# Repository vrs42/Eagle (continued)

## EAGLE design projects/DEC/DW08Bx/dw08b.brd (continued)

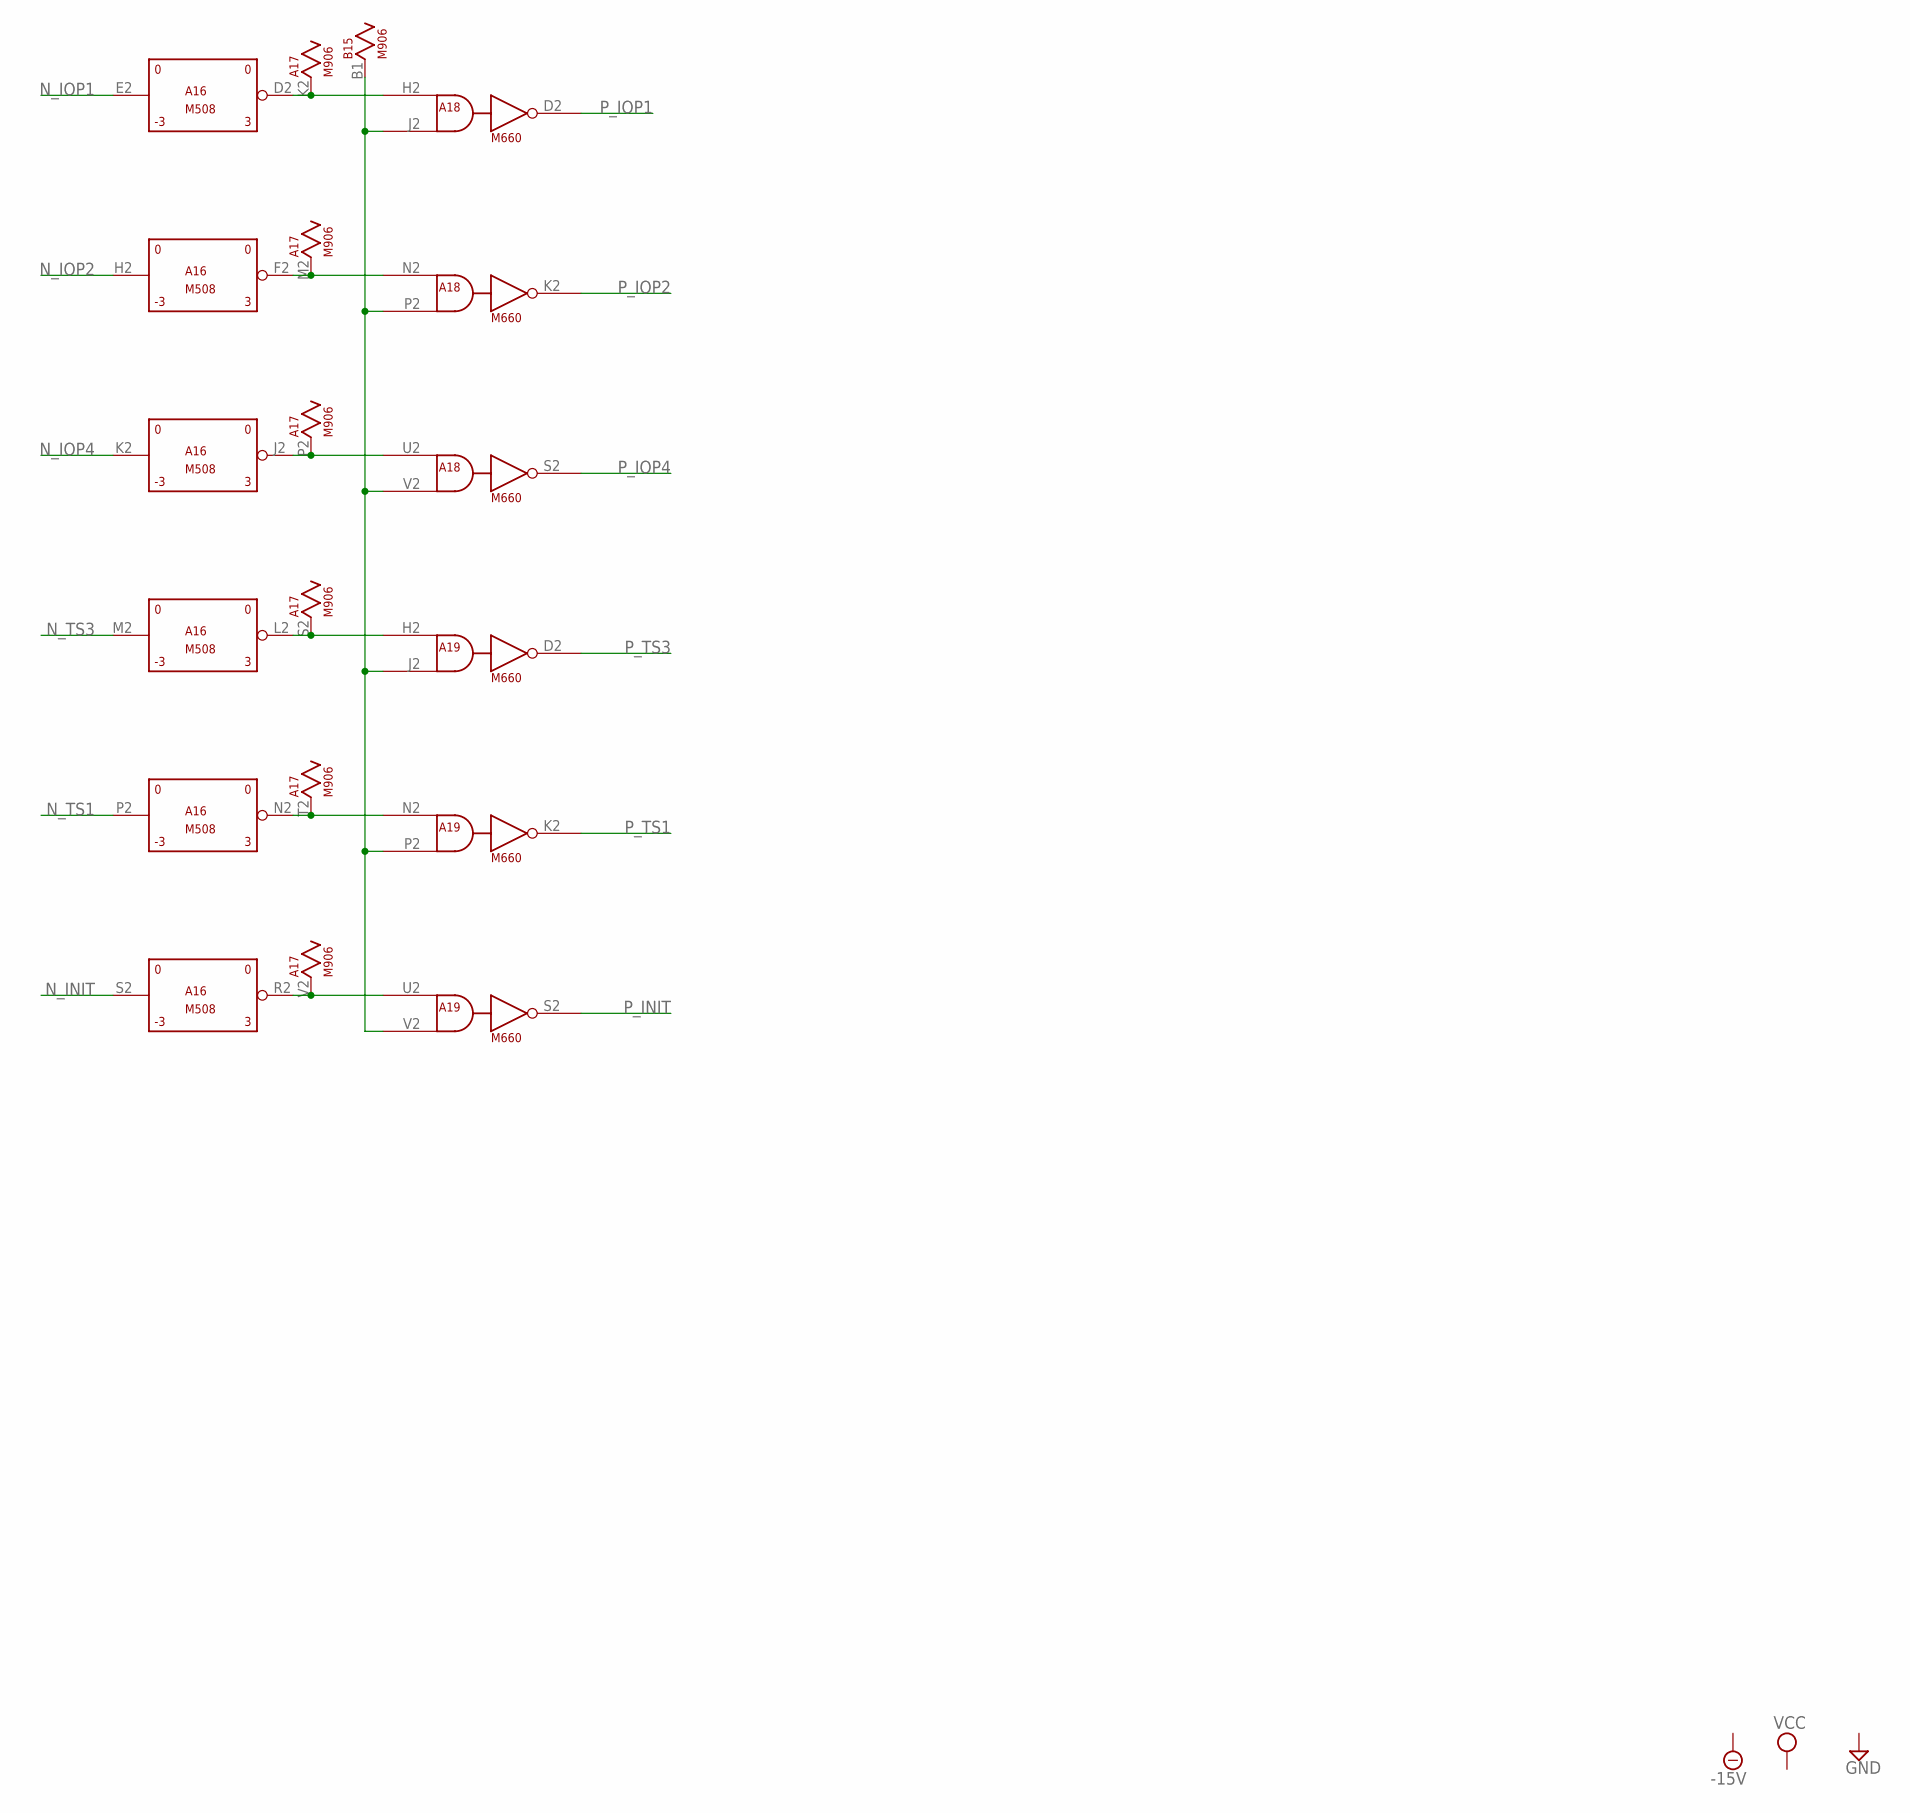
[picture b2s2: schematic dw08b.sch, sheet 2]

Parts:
A16: M508; H807
A17: M906; H807
A18, A19: M660; H807
B15: M906; H807

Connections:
-15V: A16.B2 (-15V); also elsewhere on the board
GND: A16.C2 (GND), A17.A1 (GND), A17.C1 (GND), A17.C2 (GND), A17.F1 (GND), A17.F2 (GND), A17.J2 (GND), A17.K1 (GND), A17.L2 (GND), A17.N1 (GND), A17.N2 (GND), A17.R1 (GND), A17.R2 (GND), A17.T1 (GND), A17.U2 (GND), A18.C2 (GND), A19.C2 (GND), B15.A1 (GND), B15.C1 (GND), B15.C2 (GND), B15.F1 (GND), B15.F2 (GND), B15.J2 (GND), B15.K1 (GND), B15.L2 (GND), B15.N1 (GND), B15.N2 (GND), B15.R1 (GND), B15.R2 (GND), B15.T1 (GND), B15.U2 (GND); also elsewhere on the board
unnamed: A16.D2 (OUT), A17.K2, A18.H2 (IN1)
unnamed: A16.F2 (OUT), A17.M2, A18.N2 (IN1)
unnamed: A16.J2 (OUT), A17.P2, A18.U2 (IN1)
unnamed: A16.L2 (OUT), A17.S2, A19.H2 (IN1)
unnamed: A16.N2 (OUT), A17.T2, A19.N2 (IN1)
unnamed: A16.R2 (OUT), A17.V2, A19.U2 (IN1)
unnamed: A18.J2 (IN2), A18.P2 (IN2), A18.V2 (IN2), A19.J2 (IN2), A19.P2 (IN2), A19.V2 (IN2), B15.B1
N_INIT: A16.S2 (IN); also elsewhere on the board
N_IOP1: A16.E2 (IN); also elsewhere on the board
N_IOP2: A16.H2 (IN); also elsewhere on the board
N_IOP4: A16.K2 (IN); also elsewhere on the board
N_TS1: A16.P2 (IN); also elsewhere on the board
N_TS3: A16.M2 (IN); also elsewhere on the board
P_INIT: A19.S2 (OUT); also elsewhere on the board
P_IOP1: A18.D2 (OUT); also elsewhere on the board
P_IOP2: A18.K2 (OUT); also elsewhere on the board
P_IOP4: A18.S2 (OUT); also elsewhere on the board
P_TS1: A19.K2 (OUT); also elsewhere on the board
P_TS3: A19.D2 (OUT); also elsewhere on the board
VCC: A16.A2 (VCC), A17.A2 (VCC), A18.A2 (VCC), A19.A2 (VCC), B15.A2 (VCC); also elsewhere on the board

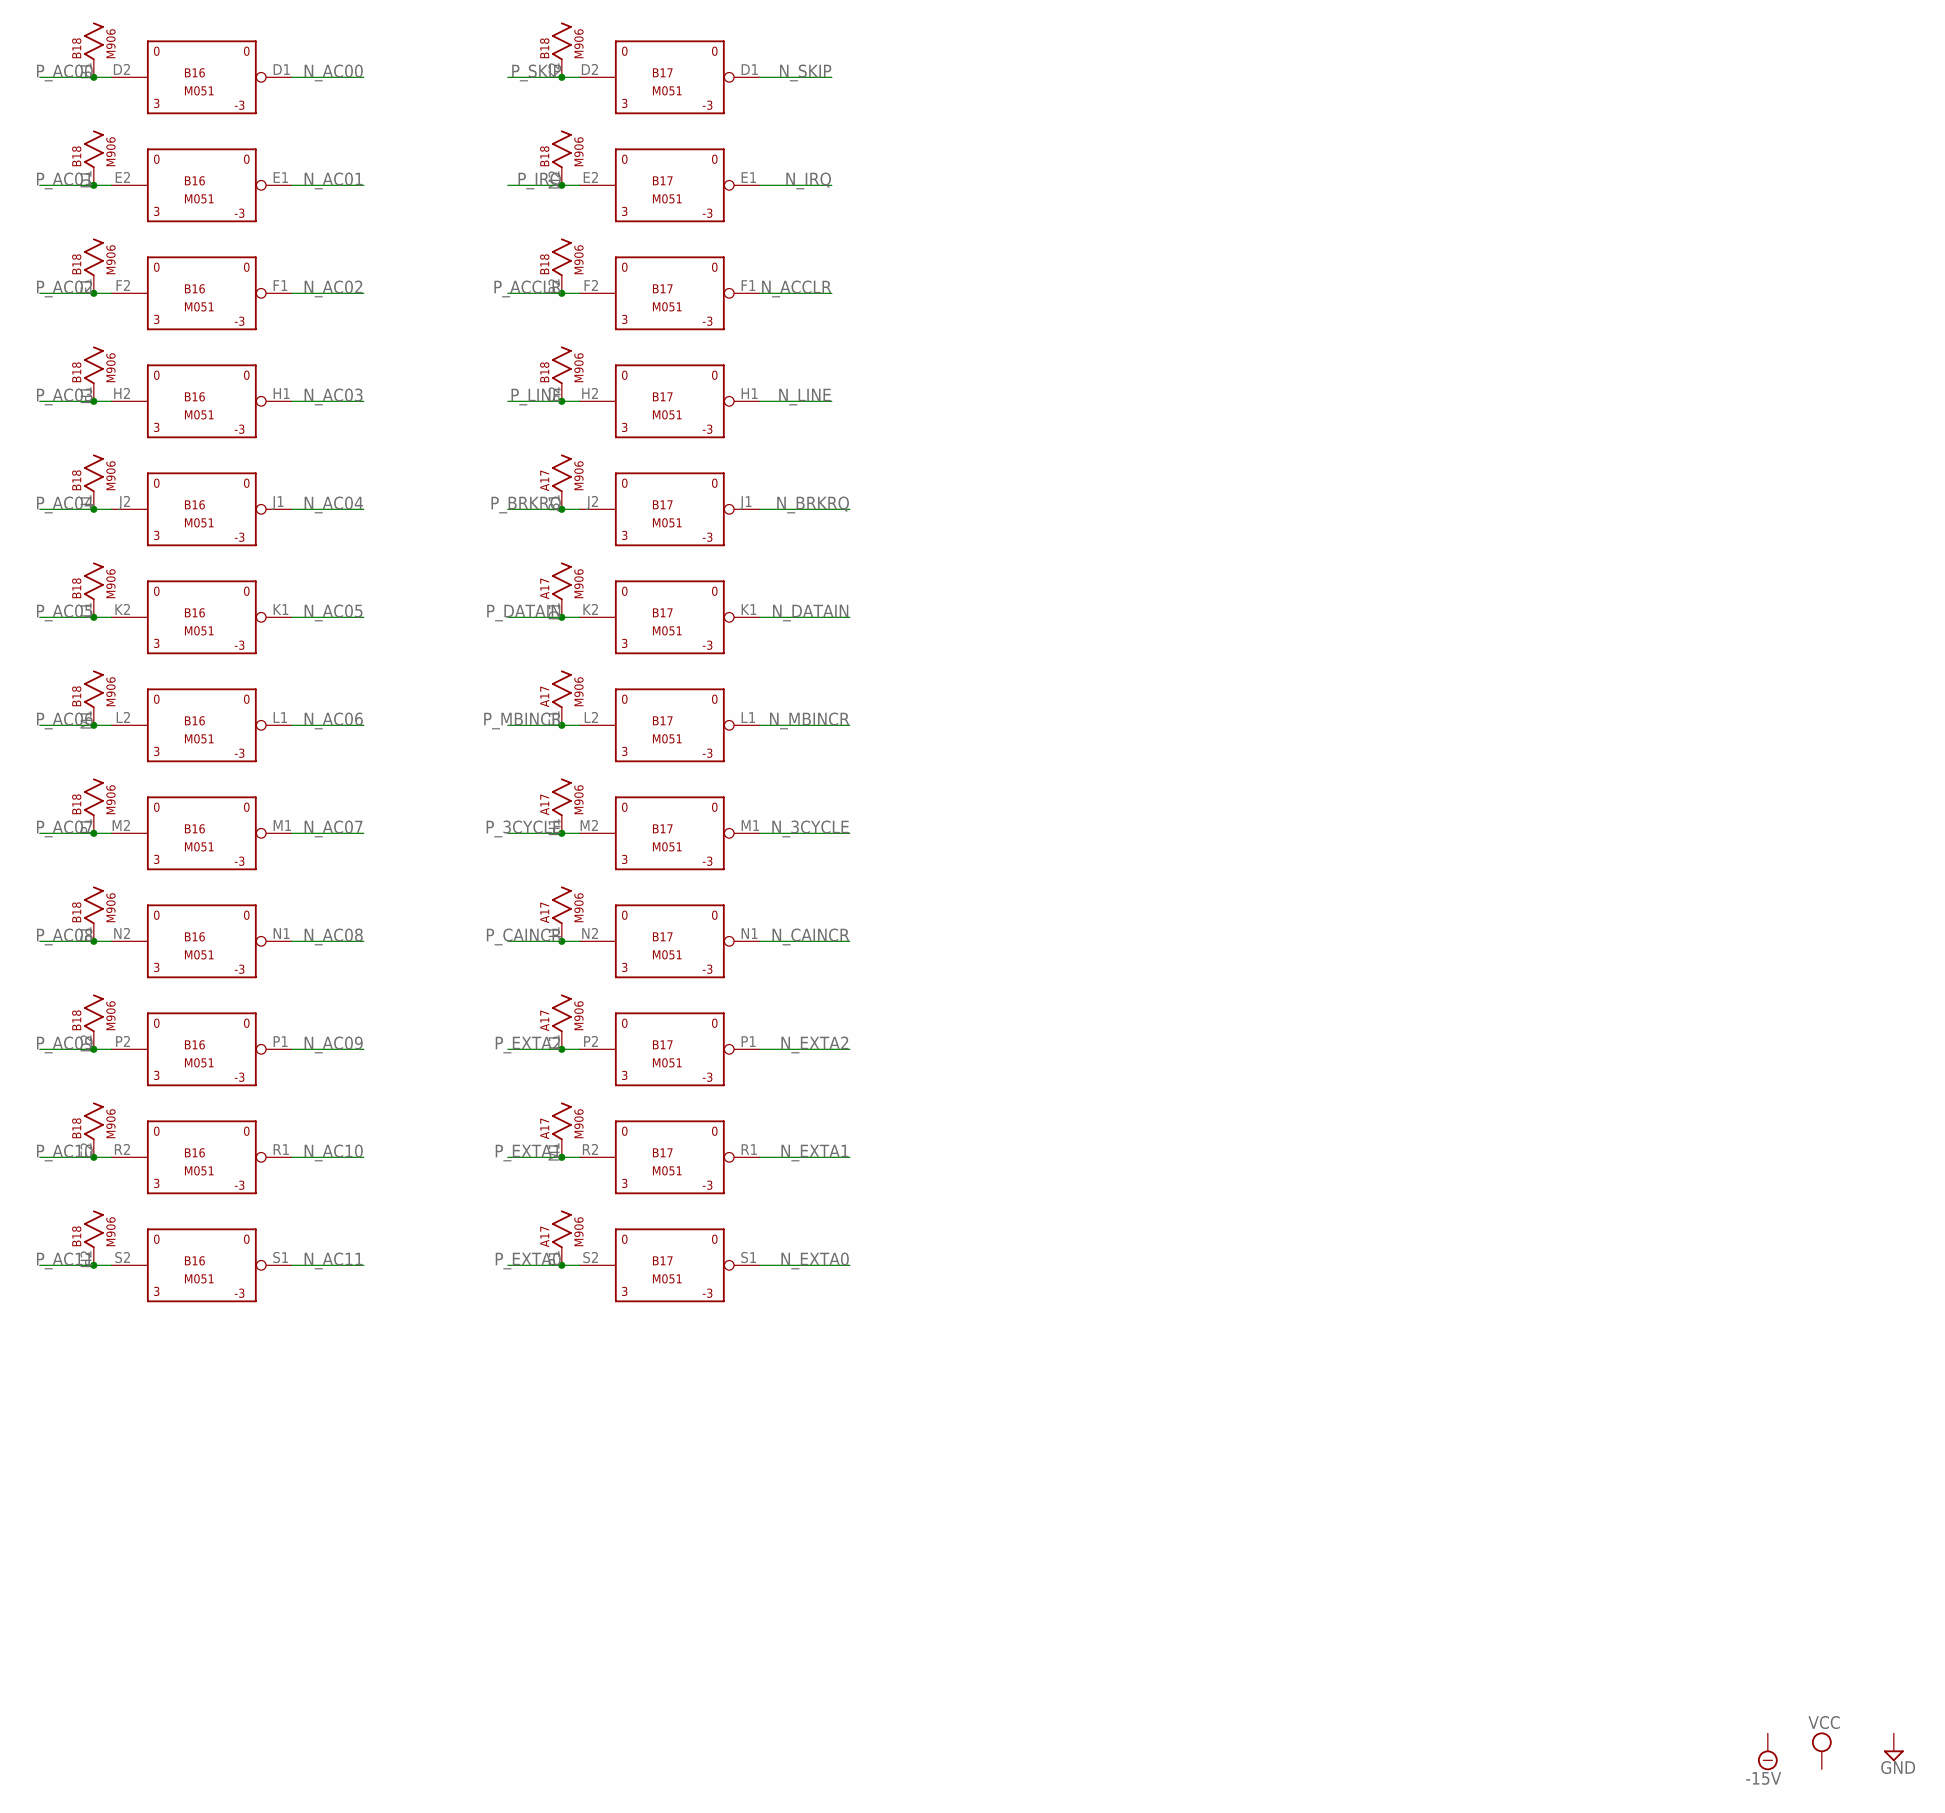
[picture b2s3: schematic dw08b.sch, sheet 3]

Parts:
A17: M906; H807
B16, B17: M051; H807
B18: M906; H807

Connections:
-15V: B16.B2 (-15V), B17.B2 (-15V); also elsewhere on the board
GND: A17.A1 (GND), A17.C1 (GND), A17.C2 (GND), A17.F1 (GND), A17.F2 (GND), A17.J2 (GND), A17.K1 (GND), A17.L2 (GND), A17.N1 (GND), A17.N2 (GND), A17.R1 (GND), A17.R2 (GND), A17.T1 (GND), A17.U2 (GND), B16.C2 (GND), B16.T1 (GND), B17.C2 (GND), B17.T1 (GND), B18.A1 (GND), B18.C1 (GND), B18.C2 (GND), B18.F1 (GND), B18.F2 (GND), B18.J2 (GND), B18.K1 (GND), B18.L2 (GND), B18.N1 (GND), B18.N2 (GND), B18.R1 (GND), B18.R2 (GND), B18.T1 (GND), B18.U2 (GND); also elsewhere on the board
N_3CYCLE: B17.M1 (OUT); also elsewhere on the board
N_AC00: B16.D1 (OUT); also elsewhere on the board
N_AC01: B16.E1 (OUT); also elsewhere on the board
N_AC02: B16.F1 (OUT); also elsewhere on the board
N_AC03: B16.H1 (OUT); also elsewhere on the board
N_AC04: B16.J1 (OUT); also elsewhere on the board
N_AC05: B16.K1 (OUT); also elsewhere on the board
N_AC06: B16.L1 (OUT); also elsewhere on the board
N_AC07: B16.M1 (OUT); also elsewhere on the board
N_AC08: B16.N1 (OUT); also elsewhere on the board
N_AC09: B16.P1 (OUT); also elsewhere on the board
N_AC10: B16.R1 (OUT); also elsewhere on the board
N_AC11: B16.S1 (OUT); also elsewhere on the board
N_ACCLR: B17.F1 (OUT); also elsewhere on the board
N_BRKRQ: B17.J1 (OUT); also elsewhere on the board
N_CAINCR: B17.N1 (OUT); also elsewhere on the board
N_DATAIN: B17.K1 (OUT); also elsewhere on the board
N_EXTA0: B17.S1 (OUT); also elsewhere on the board
N_EXTA1: B17.R1 (OUT); also elsewhere on the board
N_EXTA2: B17.P1 (OUT); also elsewhere on the board
N_IRQ: B17.E1 (OUT); also elsewhere on the board
N_LINE: B17.H1 (OUT); also elsewhere on the board
N_MBINCR: B17.L1 (OUT); also elsewhere on the board
N_SKIP: B17.D1 (OUT); also elsewhere on the board
P_3CYCLE: A17.H1, B17.M2 (IN); also elsewhere on the board
P_AC00: B16.D2 (IN), B18.B1; also elsewhere on the board
P_AC01: B16.E2 (IN), B18.D1; also elsewhere on the board
P_AC02: B16.F2 (IN), B18.E1; also elsewhere on the board
P_AC03: B16.H2 (IN), B18.H1; also elsewhere on the board
P_AC04: B16.J2 (IN), B18.J1; also elsewhere on the board
P_AC05: B16.K2 (IN), B18.L1; also elsewhere on the board
P_AC06: B16.L2 (IN), B18.M1; also elsewhere on the board
P_AC07: B16.M2 (IN), B18.P1; also elsewhere on the board
P_AC08: B16.N2 (IN), B18.S1; also elsewhere on the board
P_AC09: B16.P2 (IN), B18.D2; also elsewhere on the board
P_AC10: B16.R2 (IN), B18.E2; also elsewhere on the board
P_AC11: B16.S2 (IN), B18.H2; also elsewhere on the board
P_ACCLR: B17.F2 (IN), B18.P2; also elsewhere on the board
P_BRKRQ: A17.B1, B17.J2 (IN); also elsewhere on the board
P_CAINCR: A17.J1, B17.N2 (IN); also elsewhere on the board
P_DATAIN: A17.D1, B17.K2 (IN); also elsewhere on the board
P_EXTA0: A17.P1, B17.S2 (IN); also elsewhere on the board
P_EXTA1: A17.M1, B17.R2 (IN); also elsewhere on the board
P_EXTA2: A17.L1, B17.P2 (IN); also elsewhere on the board
P_IRQ: B17.E2 (IN), B18.M2; also elsewhere on the board
P_LINE: B17.H2 (IN), B18.S2; also elsewhere on the board
P_MBINCR: A17.E1, B17.L2 (IN); also elsewhere on the board
P_SKIP: B17.D2 (IN), B18.K2; also elsewhere on the board
VCC: A17.A2 (VCC), B16.A2 (VCC), B17.A2 (VCC), B18.A2 (VCC); also elsewhere on the board

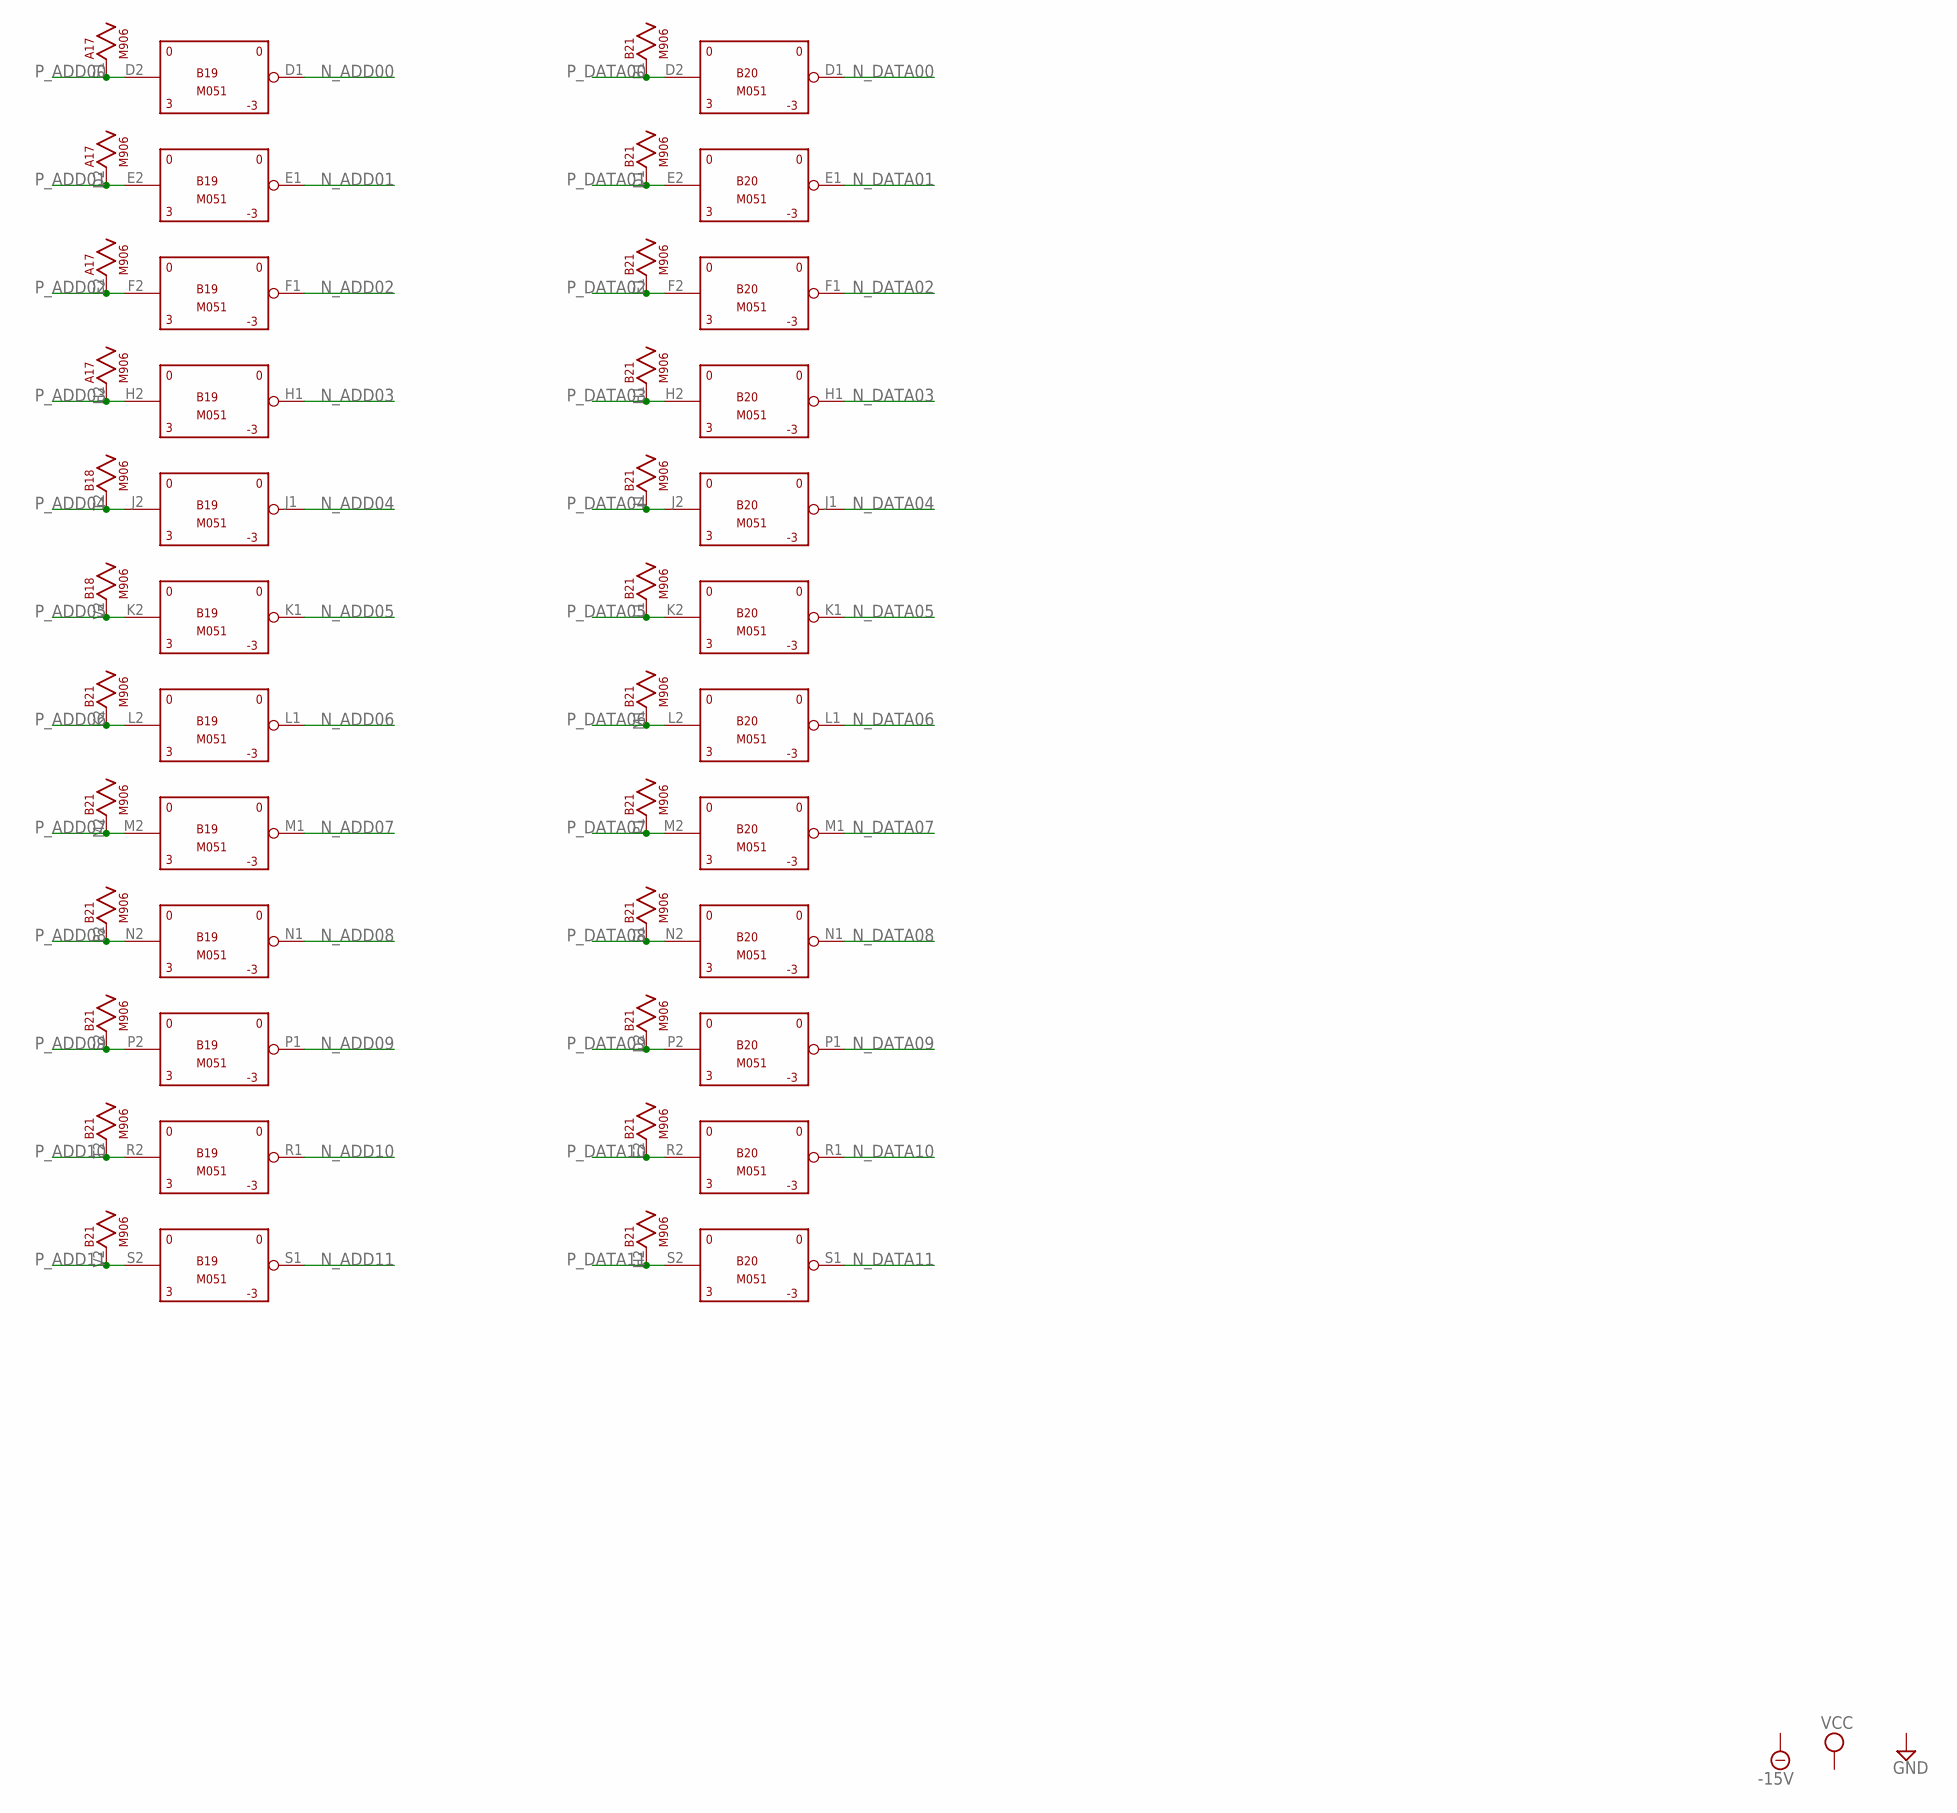
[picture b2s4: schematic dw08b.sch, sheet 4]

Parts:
A17: M906; H807
B18, B21: M906; H807
B19, B20: M051; H807

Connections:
-15V: B19.B2 (-15V), B20.B2 (-15V); also elsewhere on the board
GND: A17.A1 (GND), A17.C1 (GND), A17.C2 (GND), A17.F1 (GND), A17.F2 (GND), A17.J2 (GND), A17.K1 (GND), A17.L2 (GND), A17.N1 (GND), A17.N2 (GND), A17.R1 (GND), A17.R2 (GND), A17.T1 (GND), A17.U2 (GND), B18.A1 (GND), B18.C1 (GND), B18.C2 (GND), B18.F1 (GND), B18.F2 (GND), B18.J2 (GND), B18.K1 (GND), B18.L2 (GND), B18.N1 (GND), B18.N2 (GND), B18.R1 (GND), B18.R2 (GND), B18.T1 (GND), B18.U2 (GND), B19.C2 (GND), B19.T1 (GND), B20.C2 (GND), B20.T1 (GND), B21.A1 (GND), B21.C1 (GND), B21.C2 (GND), B21.F1 (GND), B21.F2 (GND), B21.J2 (GND), B21.K1 (GND), B21.L2 (GND), B21.N1 (GND), B21.N2 (GND), B21.R1 (GND), B21.R2 (GND), B21.T1 (GND), B21.U2 (GND); also elsewhere on the board
N_ADD00: B19.D1 (OUT); also elsewhere on the board
N_ADD01: B19.E1 (OUT); also elsewhere on the board
N_ADD02: B19.F1 (OUT); also elsewhere on the board
N_ADD03: B19.H1 (OUT); also elsewhere on the board
N_ADD04: B19.J1 (OUT); also elsewhere on the board
N_ADD05: B19.K1 (OUT); also elsewhere on the board
N_ADD06: B19.L1 (OUT); also elsewhere on the board
N_ADD07: B19.M1 (OUT); also elsewhere on the board
N_ADD08: B19.N1 (OUT); also elsewhere on the board
N_ADD09: B19.P1 (OUT); also elsewhere on the board
N_ADD10: B19.R1 (OUT); also elsewhere on the board
N_ADD11: B19.S1 (OUT); also elsewhere on the board
N_DATA00: B20.D1 (OUT); also elsewhere on the board
N_DATA01: B20.E1 (OUT); also elsewhere on the board
N_DATA02: B20.F1 (OUT); also elsewhere on the board
N_DATA03: B20.H1 (OUT); also elsewhere on the board
N_DATA04: B20.J1 (OUT); also elsewhere on the board
N_DATA05: B20.K1 (OUT); also elsewhere on the board
N_DATA06: B20.L1 (OUT); also elsewhere on the board
N_DATA07: B20.M1 (OUT); also elsewhere on the board
N_DATA08: B20.N1 (OUT); also elsewhere on the board
N_DATA09: B20.P1 (OUT); also elsewhere on the board
N_DATA10: B20.R1 (OUT); also elsewhere on the board
N_DATA11: B20.S1 (OUT); also elsewhere on the board
P_ADD00: A17.S1, B19.D2 (IN); also elsewhere on the board
P_ADD01: A17.D2, B19.E2 (IN); also elsewhere on the board
P_ADD02: A17.E2, B19.F2 (IN); also elsewhere on the board
P_ADD03: A17.H2, B19.H2 (IN); also elsewhere on the board
P_ADD04: B18.T2, B19.J2 (IN); also elsewhere on the board
P_ADD05: B18.V2, B19.K2 (IN); also elsewhere on the board
P_ADD06: B19.L2 (IN), B21.K2; also elsewhere on the board
P_ADD07: B19.M2 (IN), B21.M2; also elsewhere on the board
P_ADD08: B19.N2 (IN), B21.P2; also elsewhere on the board
P_ADD09: B19.P2 (IN), B21.S2; also elsewhere on the board
P_ADD10: B19.R2 (IN), B21.T2; also elsewhere on the board
P_ADD11: B19.S2 (IN), B21.V2; also elsewhere on the board
P_DATA00: B20.D2 (IN), B21.B1; also elsewhere on the board
P_DATA01: B20.E2 (IN), B21.D1; also elsewhere on the board
P_DATA02: B20.F2 (IN), B21.E1; also elsewhere on the board
P_DATA03: B20.H2 (IN), B21.H1; also elsewhere on the board
P_DATA04: B20.J2 (IN), B21.J1; also elsewhere on the board
P_DATA05: B20.K2 (IN), B21.L1; also elsewhere on the board
P_DATA06: B20.L2 (IN), B21.M1; also elsewhere on the board
P_DATA07: B20.M2 (IN), B21.P1; also elsewhere on the board
P_DATA08: B20.N2 (IN), B21.S1; also elsewhere on the board
P_DATA09: B20.P2 (IN), B21.D2; also elsewhere on the board
P_DATA10: B20.R2 (IN), B21.E2; also elsewhere on the board
P_DATA11: B20.S2 (IN), B21.H2; also elsewhere on the board
VCC: A17.A2 (VCC), B18.A2 (VCC), B19.A2 (VCC), B20.A2 (VCC), B21.A2 (VCC); also elsewhere on the board

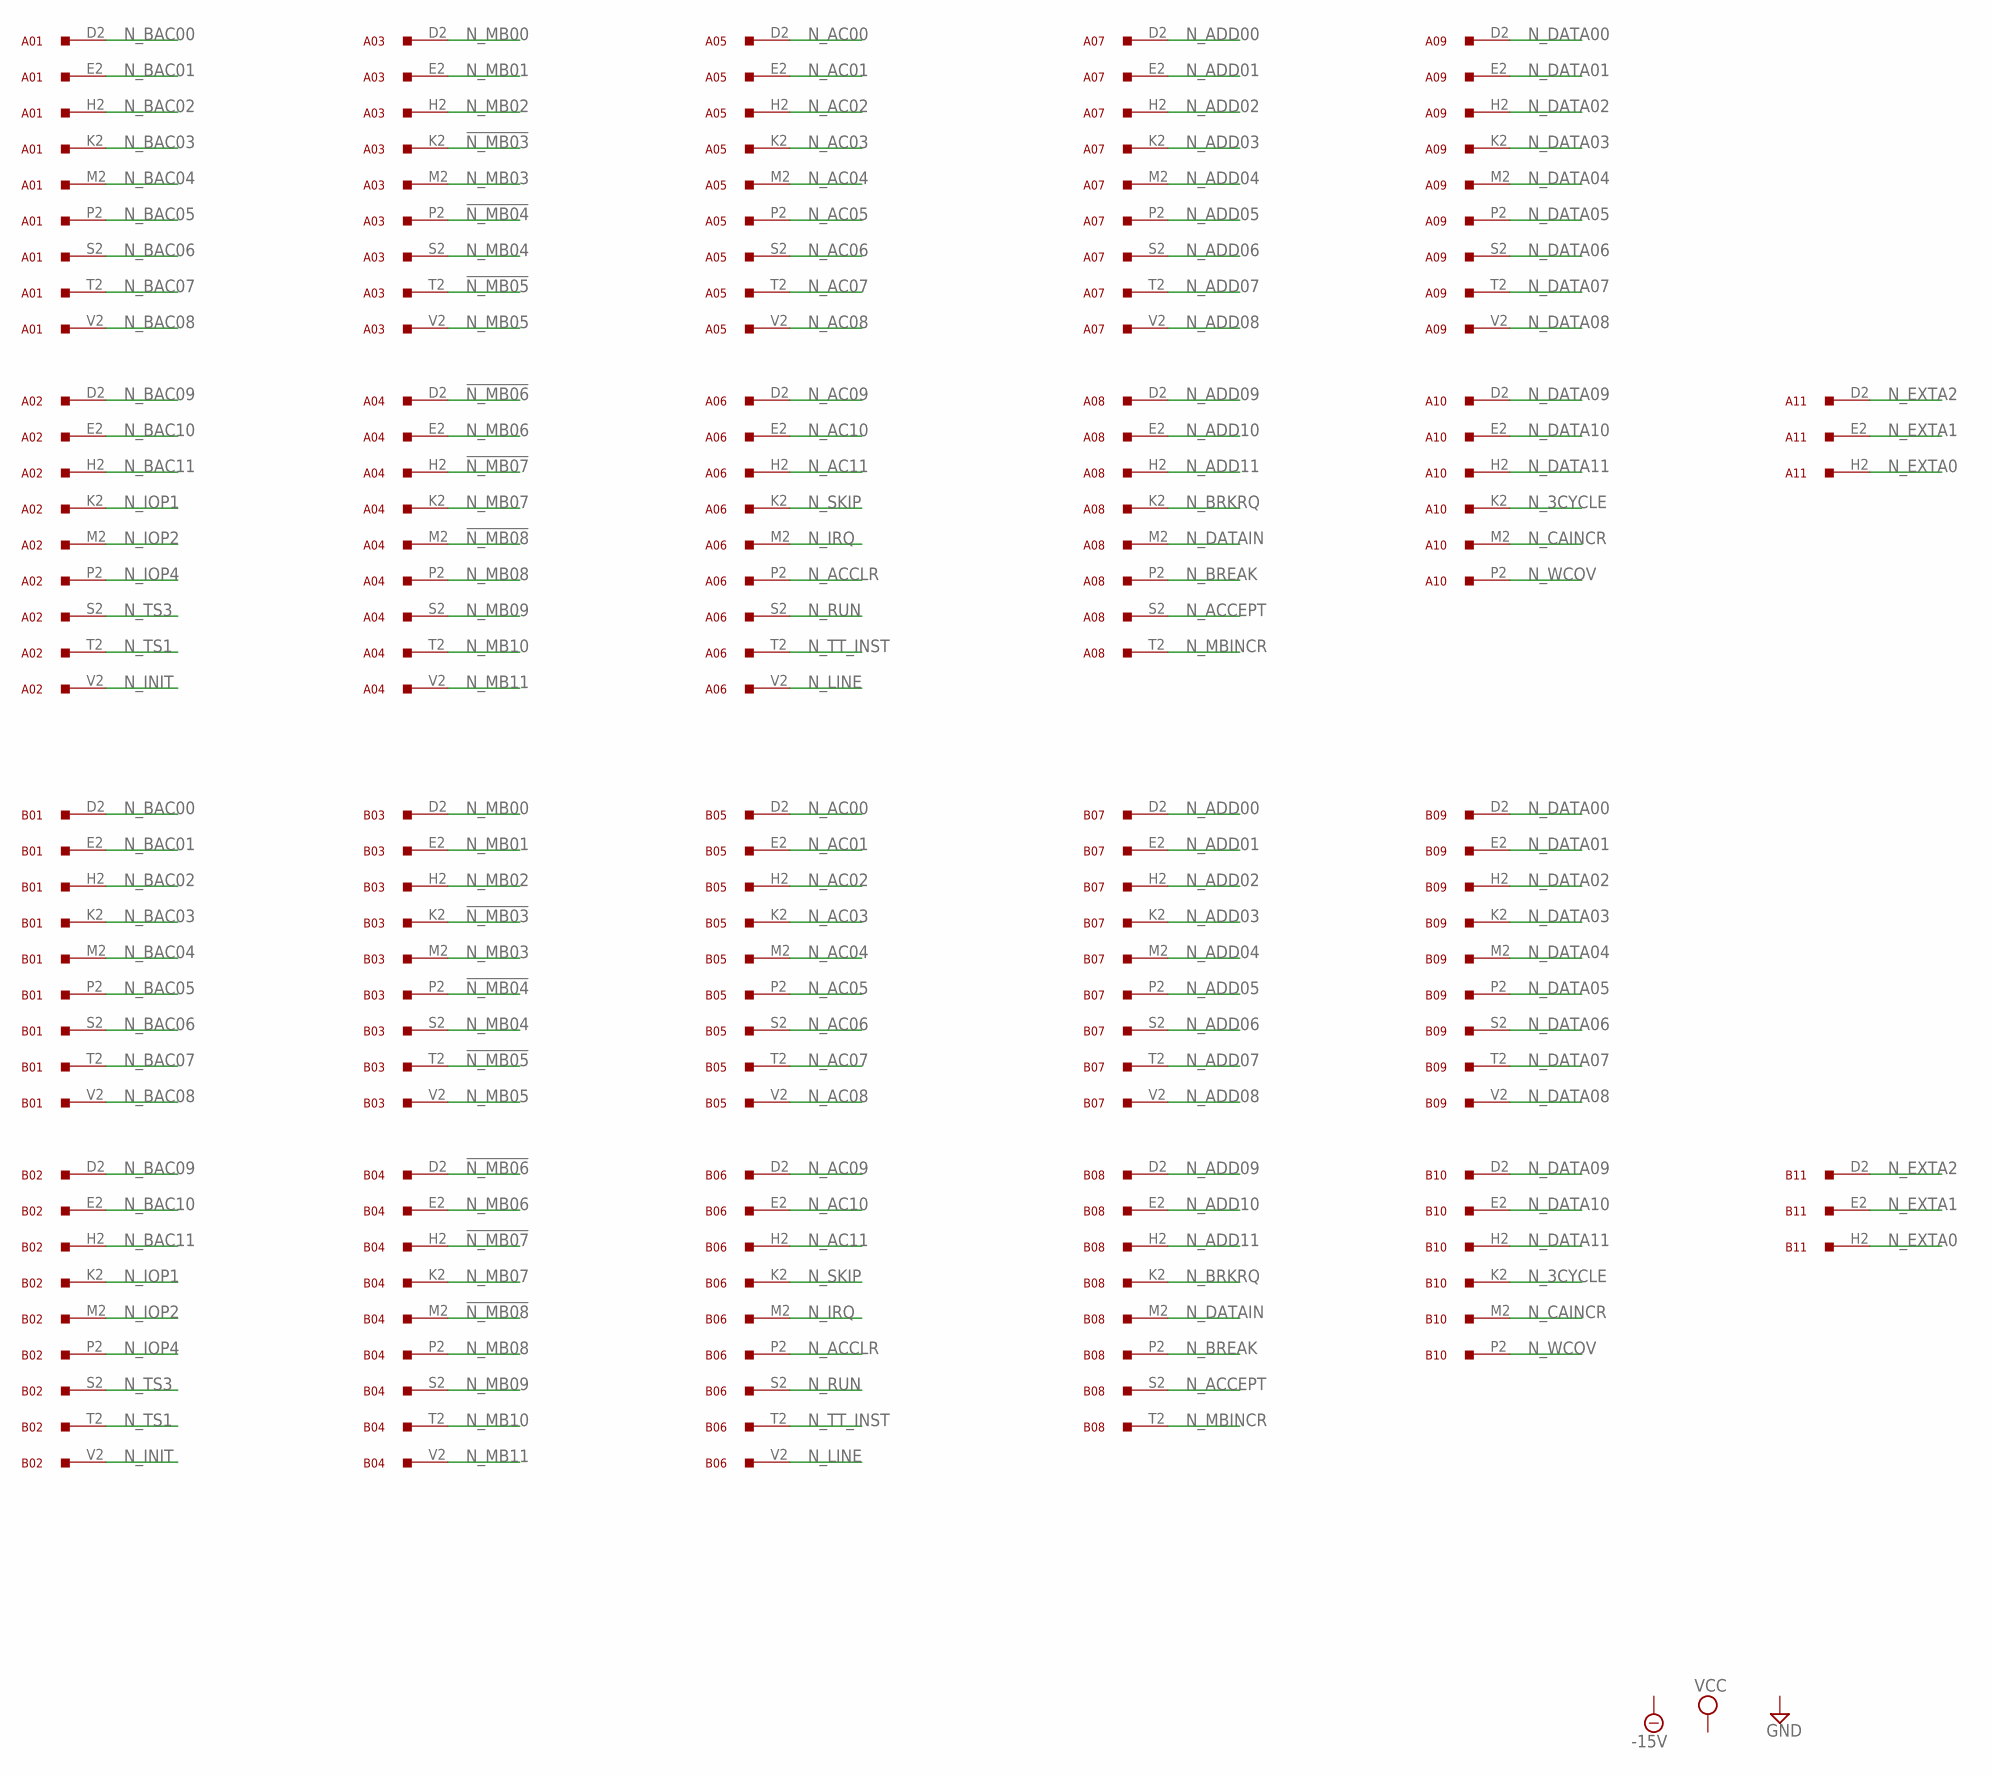
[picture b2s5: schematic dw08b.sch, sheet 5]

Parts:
A01, A02, A03, A04, A05, A06, A07, A08, A09, A10, A11: W011; H807
B01, B02, B03, B04, B05, B06, B07, B08, B09, B10, B11: W011; H807

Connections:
!N_MB03: A03.K2, B03.K2; also elsewhere on the board
!N_MB04: A03.P2, B03.P2; also elsewhere on the board
!N_MB05: A03.T2, B03.T2; also elsewhere on the board
!N_MB06: A04.D2, B04.D2; also elsewhere on the board
!N_MB07: A04.H2, B04.H2; also elsewhere on the board
!N_MB08: A04.M2, B04.M2; also elsewhere on the board
GND: A01.C2 (GND), A01.F2 (GND), A01.J2 (GND), A01.L2 (GND), A01.N2 (GND), A01.R2 (GND), A01.U2 (GND), A02.C2 (GND), A02.F2 (GND), A02.J2 (GND), A02.L2 (GND), A02.N2 (GND), A02.R2 (GND), A02.U2 (GND), A03.C2 (GND), A03.F2 (GND), A03.J2 (GND), A03.L2 (GND), A03.N2 (GND), A03.R2 (GND), A03.U2 (GND), A04.C2 (GND), A04.F2 (GND), A04.J2 (GND), A04.L2 (GND), A04.N2 (GND), A04.R2 (GND), A04.U2 (GND), A05.C2 (GND), A05.F2 (GND), A05.J2 (GND), A05.L2 (GND), A05.N2 (GND), A05.R2 (GND), A05.U2 (GND), A06.C2 (GND), A06.F2 (GND), A06.J2 (GND), A06.L2 (GND), A06.N2 (GND), A06.R2 (GND), A06.U2 (GND), A07.C2 (GND), A07.F2 (GND), A07.J2 (GND), A07.L2 (GND), A07.N2 (GND), A07.R2 (GND), A07.U2 (GND), A08.C2 (GND), A08.F2 (GND), A08.J2 (GND), A08.L2 (GND), A08.N2 (GND), A08.R2 (GND), A08.U2 (GND), A09.C2 (GND), A09.F2 (GND), A09.J2 (GND), A09.L2 (GND), A09.N2 (GND), A09.R2 (GND), A09.U2 (GND), A10.C2 (GND), A10.F2 (GND), A10.J2 (GND), A10.L2 (GND), A10.N2 (GND), A10.R2 (GND), A10.U2 (GND), A11.C2 (GND), A11.F2 (GND), A11.J2 (GND), A11.L2 (GND), A11.N2 (GND), A11.R2 (GND), A11.U2 (GND), B01.C2 (GND), B01.F2 (GND), B01.J2 (GND), B01.L2 (GND), B01.N2 (GND), B01.R2 (GND), B01.U2 (GND), B02.C2 (GND), B02.F2 (GND), B02.J2 (GND), B02.L2 (GND), B02.N2 (GND), B02.R2 (GND), B02.U2 (GND), B03.C2 (GND), B03.F2 (GND), B03.J2 (GND), B03.L2 (GND), B03.N2 (GND), B03.R2 (GND), B03.U2 (GND), B04.C2 (GND), B04.F2 (GND), B04.J2 (GND), B04.L2 (GND), B04.N2 (GND), B04.R2 (GND), B04.U2 (GND), B05.C2 (GND), B05.F2 (GND), B05.J2 (GND), B05.L2 (GND), B05.N2 (GND), B05.R2 (GND), B05.U2 (GND), B06.C2 (GND), B06.F2 (GND), B06.J2 (GND), B06.L2 (GND), B06.N2 (GND), B06.R2 (GND), B06.U2 (GND), B07.C2 (GND), B07.F2 (GND), B07.J2 (GND), B07.L2 (GND), B07.N2 (GND), B07.R2 (GND), B07.U2 (GND), B08.C2 (GND), B08.F2 (GND), B08.J2 (GND), B08.L2 (GND), B08.N2 (GND), B08.R2 (GND), B08.U2 (GND), B09.C2 (GND), B09.F2 (GND), B09.J2 (GND), B09.L2 (GND), B09.N2 (GND), B09.R2 (GND), B09.U2 (GND), B10.C2 (GND), B10.F2 (GND), B10.J2 (GND), B10.L2 (GND), B10.N2 (GND), B10.R2 (GND), B10.U2 (GND), B11.C2 (GND), B11.F2 (GND), B11.J2 (GND), B11.L2 (GND), B11.N2 (GND), B11.R2 (GND), B11.U2 (GND); also elsewhere on the board
N_3CYCLE: A10.K2, B10.K2; also elsewhere on the board
N_AC00: A05.D2, B05.D2; also elsewhere on the board
N_AC01: A05.E2, B05.E2; also elsewhere on the board
N_AC02: A05.H2, B05.H2; also elsewhere on the board
N_AC03: A05.K2, B05.K2; also elsewhere on the board
N_AC04: A05.M2, B05.M2; also elsewhere on the board
N_AC05: A05.P2, B05.P2; also elsewhere on the board
N_AC06: A05.S2, B05.S2; also elsewhere on the board
N_AC07: A05.T2, B05.T2; also elsewhere on the board
N_AC08: A05.V2, B05.V2; also elsewhere on the board
N_AC09: A06.D2, B06.D2; also elsewhere on the board
N_AC10: A06.E2, B06.E2; also elsewhere on the board
N_AC11: A06.H2, B06.H2; also elsewhere on the board
N_ACCEPT: A08.S2, B08.S2; also elsewhere on the board
N_ACCLR: A06.P2, B06.P2; also elsewhere on the board
N_ADD00: A07.D2, B07.D2; also elsewhere on the board
N_ADD01: A07.E2, B07.E2; also elsewhere on the board
N_ADD02: A07.H2, B07.H2; also elsewhere on the board
N_ADD03: A07.K2, B07.K2; also elsewhere on the board
N_ADD04: A07.M2, B07.M2; also elsewhere on the board
N_ADD05: A07.P2, B07.P2; also elsewhere on the board
N_ADD06: A07.S2, B07.S2; also elsewhere on the board
N_ADD07: A07.T2, B07.T2; also elsewhere on the board
N_ADD08: A07.V2, B07.V2; also elsewhere on the board
N_ADD09: A08.D2, B08.D2; also elsewhere on the board
N_ADD10: A08.E2, B08.E2; also elsewhere on the board
N_ADD11: A08.H2, B08.H2; also elsewhere on the board
N_BAC00: A01.D2, B01.D2; also elsewhere on the board
N_BAC01: A01.E2, B01.E2; also elsewhere on the board
N_BAC02: A01.H2, B01.H2; also elsewhere on the board
N_BAC03: A01.K2, B01.K2; also elsewhere on the board
N_BAC04: A01.M2, B01.M2; also elsewhere on the board
N_BAC05: A01.P2, B01.P2; also elsewhere on the board
N_BAC06: A01.S2, B01.S2; also elsewhere on the board
N_BAC07: A01.T2, B01.T2; also elsewhere on the board
N_BAC08: A01.V2, B01.V2; also elsewhere on the board
N_BAC09: A02.D2, B02.D2; also elsewhere on the board
N_BAC10: A02.E2, B02.E2; also elsewhere on the board
N_BAC11: A02.H2, B02.H2; also elsewhere on the board
N_BREAK: A08.P2, B08.P2; also elsewhere on the board
N_BRKRQ: A08.K2, B08.K2; also elsewhere on the board
N_CAINCR: A10.M2, B10.M2; also elsewhere on the board
N_DATA00: A09.D2, B09.D2; also elsewhere on the board
N_DATA01: A09.E2, B09.E2; also elsewhere on the board
N_DATA02: A09.H2, B09.H2; also elsewhere on the board
N_DATA03: A09.K2, B09.K2; also elsewhere on the board
N_DATA04: A09.M2, B09.M2; also elsewhere on the board
N_DATA05: A09.P2, B09.P2; also elsewhere on the board
N_DATA06: A09.S2, B09.S2; also elsewhere on the board
N_DATA07: A09.T2, B09.T2; also elsewhere on the board
N_DATA08: A09.V2, B09.V2; also elsewhere on the board
N_DATA09: A10.D2, B10.D2; also elsewhere on the board
N_DATA10: A10.E2, B10.E2; also elsewhere on the board
N_DATA11: A10.H2, B10.H2; also elsewhere on the board
N_DATAIN: A08.M2, B08.M2; also elsewhere on the board
N_EXTA0: A11.H2, B11.H2; also elsewhere on the board
N_EXTA1: A11.E2, B11.E2; also elsewhere on the board
N_EXTA2: A11.D2, B11.D2; also elsewhere on the board
N_INIT: A02.V2, B02.V2; also elsewhere on the board
N_IOP1: A02.K2, B02.K2; also elsewhere on the board
N_IOP2: A02.M2, B02.M2; also elsewhere on the board
N_IOP4: A02.P2, B02.P2; also elsewhere on the board
N_IRQ: A06.M2, B06.M2; also elsewhere on the board
N_LINE: A06.V2, B06.V2; also elsewhere on the board
N_MB00: A03.D2, B03.D2; also elsewhere on the board
N_MB01: A03.E2, B03.E2; also elsewhere on the board
N_MB02: A03.H2, B03.H2; also elsewhere on the board
N_MB03: A03.M2, B03.M2; also elsewhere on the board
N_MB04: A03.S2, B03.S2; also elsewhere on the board
N_MB05: A03.V2, B03.V2; also elsewhere on the board
N_MB06: A04.E2, B04.E2; also elsewhere on the board
N_MB07: A04.K2, B04.K2; also elsewhere on the board
N_MB08: A04.P2, B04.P2; also elsewhere on the board
N_MB09: A04.S2, B04.S2; also elsewhere on the board
N_MB10: A04.T2, B04.T2; also elsewhere on the board
N_MB11: A04.V2, B04.V2; also elsewhere on the board
N_MBINCR: A08.T2, B08.T2; also elsewhere on the board
N_RUN: A06.S2, B06.S2; also elsewhere on the board
N_SKIP: A06.K2, B06.K2; also elsewhere on the board
N_TS1: A02.T2, B02.T2; also elsewhere on the board
N_TS3: A02.S2, B02.S2; also elsewhere on the board
N_TT_INST: A06.T2, B06.T2; also elsewhere on the board
N_WCOV: A10.P2, B10.P2; also elsewhere on the board
